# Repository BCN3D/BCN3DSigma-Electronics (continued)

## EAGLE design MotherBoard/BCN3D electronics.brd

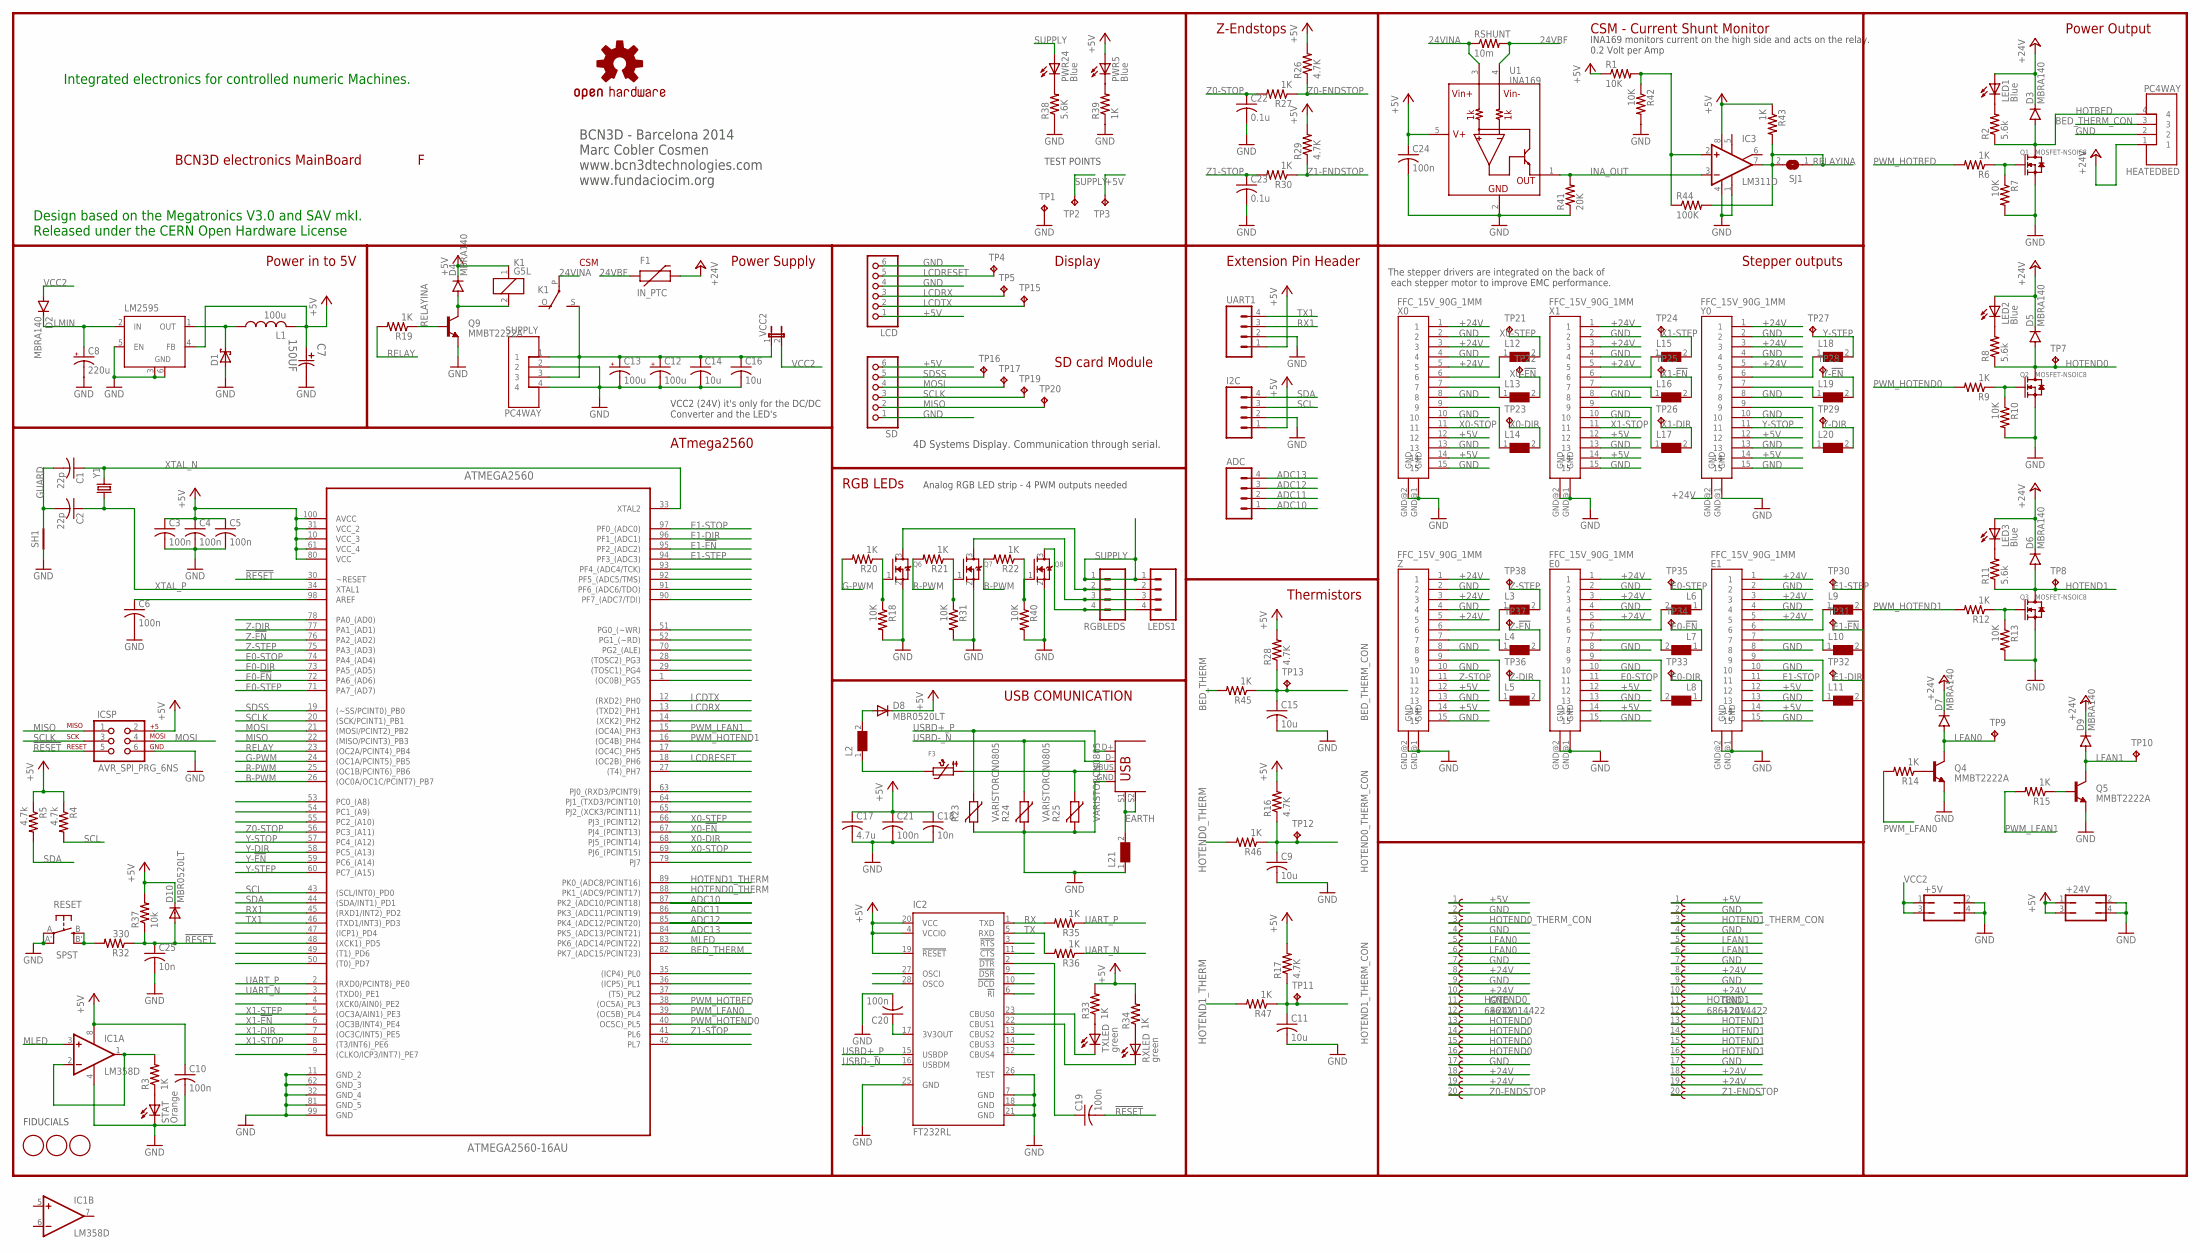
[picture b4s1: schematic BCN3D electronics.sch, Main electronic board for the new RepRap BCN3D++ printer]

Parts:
+5V, +24V: JP2Q
ADC: M04PTH; 1X04
ATMEGA2560: ATMEGA2560-16AU; QFP50P1600X1600X120-100N
C1, C2: 22p; C0805; MPN 08055A220KAT2A
C3, C4, C5, C6, C10, C19, C20, C21, C24: 100n; C0805; MPN 08055C104KAT2A
C7: 150UF; CAPAE660X610N; MPN EEEFP1A151AP
C8: 220u; UD-8X10_NICHICON; MPN EEE1VA221UAP
C9, C11, C15: 10u; C0805; MPN 08055C104KAT2A
C12, C13: 100u; UD-8X10_NICHICON; MPN EEEFC1V101AP
C14, C16: 10u; C1210K; MPN GRM32ER7YA106KA12L
C17: 4.7u; C0805; MPN 06035C103JAT2A
C18, C25: 10n; C0805; MPN 08055C103KAT2A
C22, C23: 0.1u; C0805; MPN 08055C104KAT2A
D1: SCHOTTKY-DIODESMC; SMC; MPN MBRS340T3G
D2, D3, D4, D5, D6, D7, D9: MBRA140; SMA-DIODE; MPN B140-13-F
D8, D10: MBR0520LT; SOD123; MPN DA22F2100L
E0, E1: FFC_15V_90G_1MM; TE_FFC_CON1MM
F1: IN_PTC; PTC-1206; MPN 3413.0329.22
F3: MICROBUILDER_PTC1206_L; MICROBUILDER_1206_PTC; MPN 1206L050YR
FID1, FID2, FID3: FIDUCIAL; FIDUCIAL_1MM
HEATEDBED: PC4WAY; MOLEX_MINIFIT-JR; MPN 39303045
HOTEND0, HOTEND1: 68612014422
I2C: M04PTH; 1X04
IC1: LM358D; SO08; MPN LM2904DT
IC2: FT232RL; SSOP28
IC3: LM311D; SO08
ICSP: AVR_SPI_PRG_6NS; 2X3-NS
K1: G5L; G5LE; MPN G5LA-1 5DC
L1: 100u; SSR1260; MPN SRR1260-101M
L2, L3, L4, L5, L6, L7, L8, L9, L10, L11, L12, L13, L14, L15, L16, L17, L18, L19, L20, L21: WE-CBF_0805; 0805
LCD: PINHD-1X6; 1X06
LED1, LED2, LED3: Blue; CHIPLED_0805; MPN OVS-0803
LEDS1: M04PTH; 1X04
LM2595: LM2595; TO263-5; MPN LM2595S-5.0/NOPB
LOGO1: OSHW-LOGOM; OSHW-LOGO-M
PWR5, PWR24: Blue; CHIPLED_0805; MPN OVS-0803
Q1, Q2, Q3: MOSFET-NSOIC8; SOIC8; MPN IRF8736PBF
Q4, Q5, Q9: MMBT2222A; SOT23-3; MPN BC817-40
Q6, Q7, Q8: MOSFET-NREFLOW; SOT23; MPN BSH103,215
R1, R18, R31, R40, R42: 10K; M0805; MPN CR0805-JW-102ELF
R2, R8, R11: 5.6k; M0805; MPN CR0805-JW-102ELF
R3, R39: 1K; R0805; MPN CR0805-JW-102ELF
R4, R5: 4.7k; M0805; MPN CR0805-JW-103ELF
R6, R9, R12, R14, R15, R19, R20, R21, R22, R27, R30, R33, R34, R35, R36, R43: 1K; M0805; MPN CR0805-JW-102ELF
R7, R10, R13: 10K; M0805; MPN CR0805-JW-103ELF
R16, R17, R26, R28, R29: 4.7K; M0805; MPN CR0805-FX-4701GLF
R23, R24, R25: VARISTORCN0805; CT/CN0805; MPN V5.5MLA0805LH
R32: 330; M0805; MPN CR0805-JW-103ELF
R37: 10k; M0805; MPN CR0805-JW-103ELF
R38: 5.6K; R0805; MPN CR0805-FX-4701GLF
R41: 20K; M0805; MPN CR0805-FX-4701GLF
R44: 100K; M0805; MPN CR0805-JW-102ELF
R45, R46, R47: 1K; M0805; MPN CR0805-FX-4701GLF
RESET: SPST; EVQ-Q2; MPN EVQQ2503W
RGBLEDS: M04PTH; 1X04
RSHUNT: 10m; R2512
RXLED: green; CHIPLED_0805; MPN 150080VS75000
SD: PINHD-1X6; 1X06
SH1: SHORTT5; SHORT_TOP-50
SJ1: SJ
STAT: Orange; CHIP-LED0805; MPN KP-2012SECK
SUPPLY: PC4WAY; MOLEX_MINIFIT-JR; MPN 39303045
TP1, TP2, TP3, TP4, TP5, TP7, TP8, TP9, TP10, TP11, TP12, TP13, TP15, TP16, TP17, TP19, TP20, TP21, TP22, TP23, TP24, TP25, TP26, TP27, TP28, TP29, TP30, TP31, TP32, TP33, TP34, TP35, TP36, TP37, TP38: TPB2,54; B2,54
TXLED: green; CHIPLED_0805; MPN 150080VS75000
U1: INA169; SOT23-5
U$6: USB+SHIELD; USB-B-PTH; MPN 67068-8000
UART1: M04PTH; 1X04
VCC2: JP1E; JP1
X0, X1: FFC_15V_90G_1MM; TE_FFC_CON1MM
Y0: FFC_15V_90G_1MM; TE_FFC_CON1MM
Y1: CRYSTALHC49US; HC49US; MPN 9B-16.000MAAJ-B
Z: FFC_15V_90G_1MM; TE_FFC_CON1MM

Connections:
24VBF: F1.1, RSHUNT.2, U1.4 (VIN-)
24VINA: K1.P, RSHUNT.1, U1.3 (VIN+)
!RESET: ATMEGA2560.30 (~RESET), C19.2, C25.1, D10.A, ICSP.5, R32.1, R37.1
+5V: +24V.1, +24V.3, ATMEGA2560.10 (VCC_3), ATMEGA2560.31 (VCC_2), ATMEGA2560.61 (VCC_4), ATMEGA2560.80 (VCC), ATMEGA2560.100 (AVCC), C3.1, C4.1, C5.1, C7.1, C10.1, C17.1, C18.1, C21.1, C24.1, D4.C, D8.C, D10.C, E0.12, E0.14, E1.12, E1.14, HOTEND0.1, HOTEND1.1, I2C.1, IC1.8 (V+), IC2.4 (VCCIO), IC2.19 (!RESET), IC2.20 (VCC), IC3.8 (V+), ICSP.2, K1.1, L1.B (2), LCD.1, LM2595.4 (FB), PWR5.A, R1.1, R4.1, R5.1, R16.2, R17.2, R26.2, R28.2, R29.2, R33.2, R34.2, R37.2, R43.1, SD.6, TP3.TP, U1.5 (V+), UART1.1, X0.12, X0.14, X1.12, X1.14, Y0.12, Y0.14, Z.12, Z.14
+24V: D3.C, D5.C, D6.C, D7.C, D9.C, E0.1, E0.3, E0.5, E1.1, E1.3, E1.5, F1.2, HEATEDBED.1, HOTEND0.8, HOTEND0.10, HOTEND0.12, HOTEND0.18, HOTEND0.19, HOTEND1.8, HOTEND1.10, HOTEND1.12, HOTEND1.18, HOTEND1.19, LED1.A, LED2.A, LED3.A, X0.1, X0.3, X0.5, X1.1, X1.3, X1.5, Y0.1, Y0.3, Y0.5, Y0.GND@2 (GND), Z.1, Z.3, Z.5
ADC10: ADC.1, ATMEGA2560.87 (PK2_(ADC10/PCINT18))
ADC11: ADC.2, ATMEGA2560.86 (PK3_(ADC11/PCINT19))
ADC12: ADC.3, ATMEGA2560.85 (PK4_(ADC12/PCINT20))
ADC13: ADC.4, ATMEGA2560.84 (PK5_(ADC13/PCINT21))
B-PWM: ATMEGA2560.26 ((OC0A/OC1C/PCINT7)_PB7), R22.2
BED_THERM: ATMEGA2560.82 (PK7_(ADC15/PCINT23)), R45.2
BED_THERM_CON: C15.1, HEATEDBED.3, R28.1, R45.1, TP13.TP
E0-!EN: ATMEGA2560.72 (PA6_(AD6)), L7.1, TP34.TP
E0-DIR: ATMEGA2560.73 (PA5_(AD5)), L8.1, TP33.TP
E0-STEP: ATMEGA2560.71 (PA7_(AD7)), L6.1, TP35.TP
E0-STOP: ATMEGA2560.74 (PA4_(AD4)), E0.11
E1-!EN: ATMEGA2560.95 (PF2_(ADC2)), L10.2, TP31.TP
E1-DIR: ATMEGA2560.96 (PF1_(ADC1)), L11.2, TP32.TP
E1-STEP: ATMEGA2560.94 (PF3_(ADC3)), L9.2, TP30.TP
E1-STOP: ATMEGA2560.97 (PF0_(ADC0)), E1.11
EARTH: L21.2, U$6.S1, U$6.S2
G-PWM: ATMEGA2560.24 ((OC1A/PCINT5)_PB5), R20.2
GND: +5V.2, +5V.4, +24V.2, +24V.4, ATMEGA2560.11 (GND_2), ATMEGA2560.32 (GND_4), ATMEGA2560.62 (GND_3), ATMEGA2560.81 (GND_5), ATMEGA2560.99 (GND), C3.2, C4.2, C5.2, C6.2, C7.2, C8.-, C9.2, C10.2, C11.2, C12.-, C13.-, C14.2, C15.2, C16.2, C17.2, C18.2, C20.2, C21.2, C22.2, C23.2, C24.2, C25.2, D1.A, E0.2, E0.4, E0.8, E0.10, E0.13, E0.15, E0.GND@1 (GND), E0.GND@2 (GND), E1.2, E1.4, E1.8, E1.10, E1.13, E1.15, E1.GND@1 (GND), E1.GND@2 (GND), HEATEDBED.2, HOTEND0.2, HOTEND0.4, HOTEND0.7, HOTEND0.9, HOTEND0.11, HOTEND0.17, HOTEND1.2, HOTEND1.4, HOTEND1.7, HOTEND1.9, HOTEND1.11, HOTEND1.17, I2C.2, IC1.4 (V-), IC2.7 (GND), IC2.18 (GND), IC2.21 (GND), IC2.25 (GND), IC2.26 (TEST), IC3.1 (GND), IC3.4 (V-), ICSP.6, L21.1, LCD.4, LCD.6, LM2595.3 (GND), LM2595.5 (EN), LM2595.6 (GND), Q1.1 (S), Q1.2 (S), Q1.3 (S), Q2.1 (S), Q2.2 (S), Q2.3 (S), Q3.1 (S), Q3.2 (S), Q3.3 (S), Q4.2 (E), Q5.2 (E), Q6.2 (S), Q7.2 (S), Q8.2 (S), Q9.2 (E), R7.2, R10.2, R13.2, R18.2, R23.2, R24.2, R25.2, R31.2, R38.1, R39.1, R40.2, R41.1, R42.2, RESET.A, RESET.A' (P1), SD.1, SH1.1, STAT.C, SUPPLY.2, SUPPLY.4, TP1.TP, U1.2 (GND), U$6.GND, UART1.2, X0.2, X0.4, X0.8, X0.10, X0.13, X0.15, X0.GND@1 (GND), X0.GND@2 (GND), X1.2, X1.4, X1.8, X1.10, X1.13, X1.15, X1.GND@1 (GND), X1.GND@2 (GND), Y0.2, Y0.4, Y0.8, Y0.10, Y0.13, Y0.15, Y0.GND@1 (GND), Z.2, Z.4, Z.8, Z.10, Z.13, Z.15, Z.GND@1 (GND), Z.GND@2 (GND)
GUARD: C1.2, C2.2, SH1.2
HOTBED: D3.A, HEATEDBED.4, Q1.5 (D), Q1.6 (D), Q1.7 (D), Q1.8 (D), R2.1
HOTEND0: D5.A, HOTEND0.13, HOTEND0.14, HOTEND0.15, HOTEND0.16, Q2.5 (D), Q2.6 (D), Q2.7 (D), Q2.8 (D), R8.1, TP7.TP
HOTEND0_THERM: ATMEGA2560.88 (PK1_(ADC9/PCINT17)), R46.2
HOTEND0_THERM_CON: C9.1, HOTEND0.3, R16.1, R46.1, TP12.TP
HOTEND1: D6.A, HOTEND1.13, HOTEND1.14, HOTEND1.15, HOTEND1.16, Q3.5 (D), Q3.6 (D), Q3.7 (D), Q3.8 (D), R11.1, TP8.TP
HOTEND1_THERM: ATMEGA2560.89 (PK0_(ADC8/PCINT16)), R47.2
HOTEND1_THERM_CON: C11.1, HOTEND1.3, R17.1, R47.1, TP11.TP
INA_OUT: IC3.3 (-IN), R41.2, U1.1 (OUT)
LCDRESET: ATMEGA2560.18 ((OC2B)_PH6), LCD.5, TP4.TP
LCDRX: ATMEGA2560.13 ((TXD2)_PH1), LCD.3, TP5.TP
LCDTX: ATMEGA2560.12 ((RXD2)_PH0), LCD.2, TP15.TP
LFAN0: D7.A, HOTEND0.5, HOTEND0.6, Q4.3 (C), TP9.TP
LFAN1: D9.A, HOTEND1.5, HOTEND1.6, Q5.3 (C), TP10.TP
LMIN: C8.+, D2.C, LM2595.2 (IN)
MISO: ATMEGA2560.22 ((MISO/PCINT3)_PB3), ICSP.1, SD.2, TP20.TP
MLED: ATMEGA2560.83 (PK6_(ADC14/PCINT22)), IC1.3 (+IN)
MOSI: ATMEGA2560.21 ((MOSI/PCINT2)_PB2), ICSP.4, SD.4, TP17.TP
unnamed: C19.1, IC2.2 (!DTR)
unnamed: ATMEGA2560.98 (AREF), C6.1
unnamed: L12.1, X0.6
unnamed: IC2.23 (CBUS0), TXLED.C
unnamed: IC2.22 (CBUS1), RXLED.C
unnamed: LEDS1.2, Q6.3 (D), RGBLEDS.2
unnamed: LEDS1.3, Q7.3 (D), RGBLEDS.3
unnamed: LEDS1.4, Q8.3 (D), RGBLEDS.4
unnamed: R32.2, RESET.B (S), RESET.B' (S1)
unnamed: D8.A, L2.2
unnamed: IC1.1 (OUT), IC1.2 (-IN), R3.2
unnamed: Q6.1 (G), R18.1, R20.1
unnamed: R3.1, STAT.A
unnamed: Q7.1 (G), R21.1, R31.1
unnamed: Q8.1 (G), R22.1, R40.1
unnamed: L13.1, X0.7
unnamed: L14.1, X0.9
unnamed: L18.1, Y0.6
unnamed: L19.1, Y0.7
unnamed: L20.1, Y0.9
unnamed: L15.1, X1.6
unnamed: L16.1, X1.7
unnamed: L17.1, X1.9
unnamed: E0.6, L6.2
unnamed: E0.7, L7.2
unnamed: E0.9, L8.2
unnamed: F3.2, L2.1
unnamed: IC3.2 (+IN), R1.2, R42.1, R44.1
unnamed: L3.1, Z.6
unnamed: L4.1, Z.7
unnamed: L5.1, Z.9
unnamed: E1.9, L11.1
unnamed: E1.7, L10.1
unnamed: E1.6, L9.1
unnamed: LED1.C, R2.2
unnamed: Q1.4 (G), R6.1, R7.1
unnamed: C20.1, IC2.17 (3V3OUT)
unnamed: R33.1, TXLED.A
unnamed: R34.1, RXLED.A
unnamed: Q4.1 (B), R14.1
unnamed: LED2.C, R8.2
unnamed: Q2.4 (G), R9.1, R10.1
unnamed: D4.A, K1.2, Q9.3 (C)
unnamed: LED3.C, R11.2
unnamed: Q3.4 (G), R12.1, R13.1
unnamed: Q5.1 (B), R15.1
unnamed: PWR24.C, R38.2
unnamed: PWR5.C, R39.2
OUT: D1.C, L1.A (1), LM2595.1 (OUT)
PWM_HOTBED: ATMEGA2560.38 ((OC5A)_PL3), R6.2
PWM_HOTEND0: ATMEGA2560.40 (OC5C)_PL5), R9.2
PWM_HOTEND1: ATMEGA2560.16 ((OC4B)_PH4), R12.2
PWM_LFAN0: ATMEGA2560.39 ((OC5B)_PL4), R14.2
PWM_LFAN1: ATMEGA2560.15 ((OC4A)_PH3), R15.2
R-PWM: ATMEGA2560.25 ((OC1B/PCINT6)_PB6), R21.2
RELAY: ATMEGA2560.23 ((OC2A/PCINT4)_PB4), R19.2
RELAYINA: IC3.7 (OUT), Q9.1 (B), R19.1, R43.2, R44.2, SJ1.1, SJ1.2
RX: IC2.1 (TXD), R35.2
RX1: ATMEGA2560.45 ((RXD1/INT2)_PD2), UART1.3
SCL: ATMEGA2560.43 ((SCL/INT0)_PD0), I2C.3, R4.2
SCLK: ATMEGA2560.20 ((SCK/PCINT1)_PB1), ICSP.3, SD.3, TP19.TP
SDA: ATMEGA2560.44 ((SDA/INT1)_PD1), I2C.4, R5.2
SDSS: ATMEGA2560.19 ((~SS/PCINT0)_PB0), SD.5, TP16.TP
SUPPLY: C12.+, C13.+, C14.1, C16.1, K1.S, LEDS1.1, PWR24.A, RGBLEDS.1, SUPPLY.1, SUPPLY.3, TP2.TP, VCC2.1
TX: IC2.5 (RXD), R36.2
TX1: ATMEGA2560.46 ((TXD1/INT3)_PD3), UART1.4
UART_N: ATMEGA2560.3 ((TXD0)_PE1), R36.1
UART_P: ATMEGA2560.2 ((RXD0/PCINT8)_PE0), R35.1
USBD+_P: IC2.15 (USBDP), R23.1, U$6.D+
USBD-_N: IC2.16 (USBDM), R24.1, U$6.D-
VBUS: F3.1, R25.1, U$6.VBUS
VCC2: +5V.1, +5V.3, D2.A, VCC2.2
X0-!EN: ATMEGA2560.67 (PJ4_(PCINT13)), L13.2, TP22.TP
X0-DIR: ATMEGA2560.68 (PJ5_(PCINT14)), L14.2, TP23.TP
X0-STEP: ATMEGA2560.66 (PJ3_(PCINT12)), L12.2, TP21.TP
X0-STOP: ATMEGA2560.69 (PJ6_(PCINT15)), X0.11
X1-!EN: ATMEGA2560.6 ((OC3B/INT4)_PE4), L16.2, TP25.TP
X1-DIR: ATMEGA2560.7 ((OC3C/INT5)_PE5), L17.2, TP26.TP
X1-STEP: ATMEGA2560.5 ((OC3A/AIN1)_PE3), L15.2, TP24.TP
X1-STOP: ATMEGA2560.8 ((T3/INT6)_PE6), X1.11
XTAL_N: ATMEGA2560.33 (XTAL2), C1.1, Y1.2
XTAL_P: ATMEGA2560.34 (XTAL1), C2.1, Y1.1
Y-!EN: ATMEGA2560.59 (PC6_(A14)), L19.2, TP28.TP
Y-DIR: ATMEGA2560.58 (PC5_(A13)), L20.2, TP29.TP
Y-STEP: ATMEGA2560.60 (PC7_(A15)), L18.2, TP27.TP
Y-STOP: ATMEGA2560.57 (PC4_(A12)), Y0.11
Z0-ENDSTOP: HOTEND0.20, R26.1, R27.1
Z0-STOP: ATMEGA2560.56 (PC3_(A11)), C22.1, R27.2
Z1-ENDSTOP: HOTEND1.20, R29.1, R30.1
Z1-STOP: ATMEGA2560.41 (PL6), C23.1, R30.2
Z-!EN: ATMEGA2560.76 (PA2_(AD2)), L4.2, TP37.TP
Z-DIR: ATMEGA2560.77 (PA1_(AD1)), L5.2, TP36.TP
Z-STEP: ATMEGA2560.75 (PA3_(AD3)), L3.2, TP38.TP
Z-STOP: Z.11

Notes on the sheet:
Power Output
Thermistors
USB COMUNICATION
ATmega2560
Power in to 5V
Power Supply
Display
TEST POINTS
FIDUCIALS
SD card Module
Extension Pin Header
4D Systems Display. Communication through serial.
BCN3D - Barcelona 2014 Marc Cobler Cosmen www.bcn3dtechnologies.com www.fundaciocim.org
Design based on the Megatronics V3.0 and SAV mkI. Released under the CERN Open Hardware License
Integrated electronics for controlled numeric Machines.
Stepper outputs
The stepper drivers are integrated on the back of each stepper motor to improve EMC performance.
BCN3D electronics MainBoard
RGB LEDs
Analog RGB LED strip - 4 PWM outputs needed
VCC2 (24V) it's only for the DC/DC Converter and the LED's
Z-Endstops
CSM - Current Shunt Monitor
INA169 monitors current on the high side and acts on the relay. 0.2 Volt per Amp
CSM

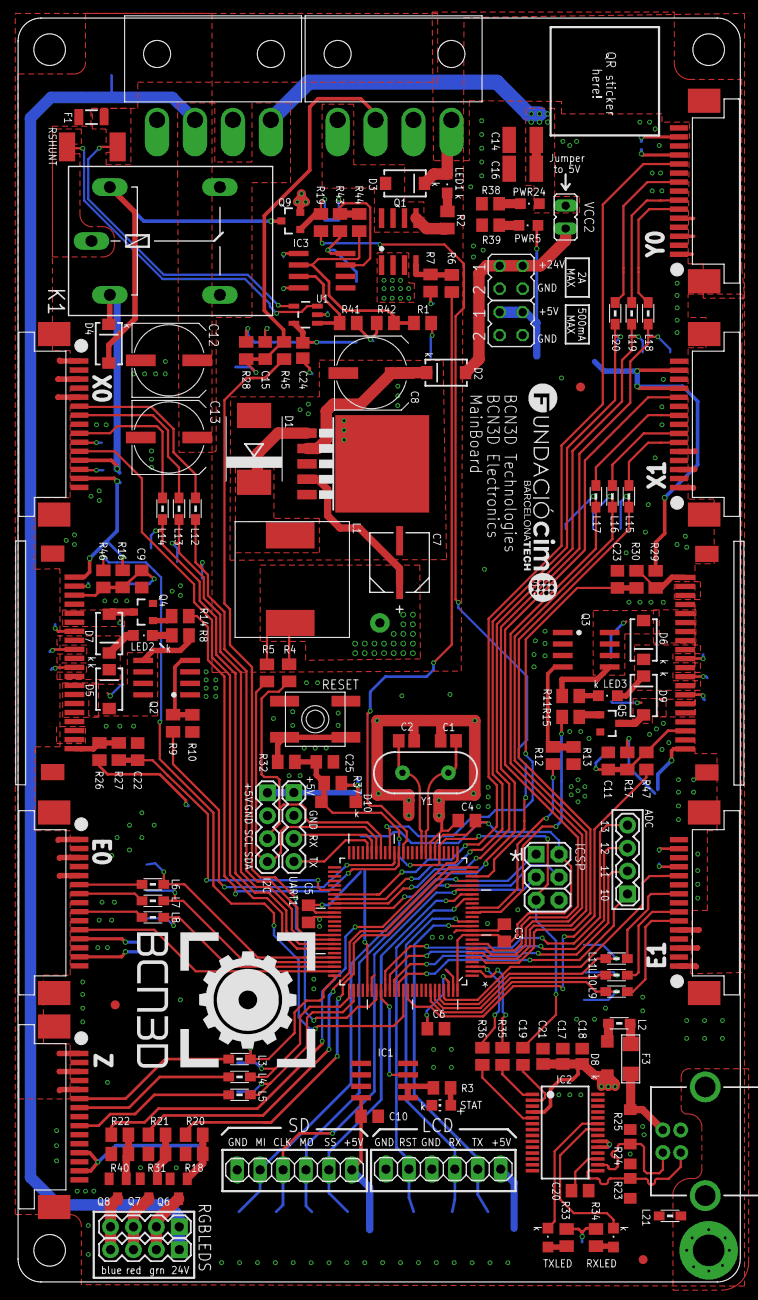
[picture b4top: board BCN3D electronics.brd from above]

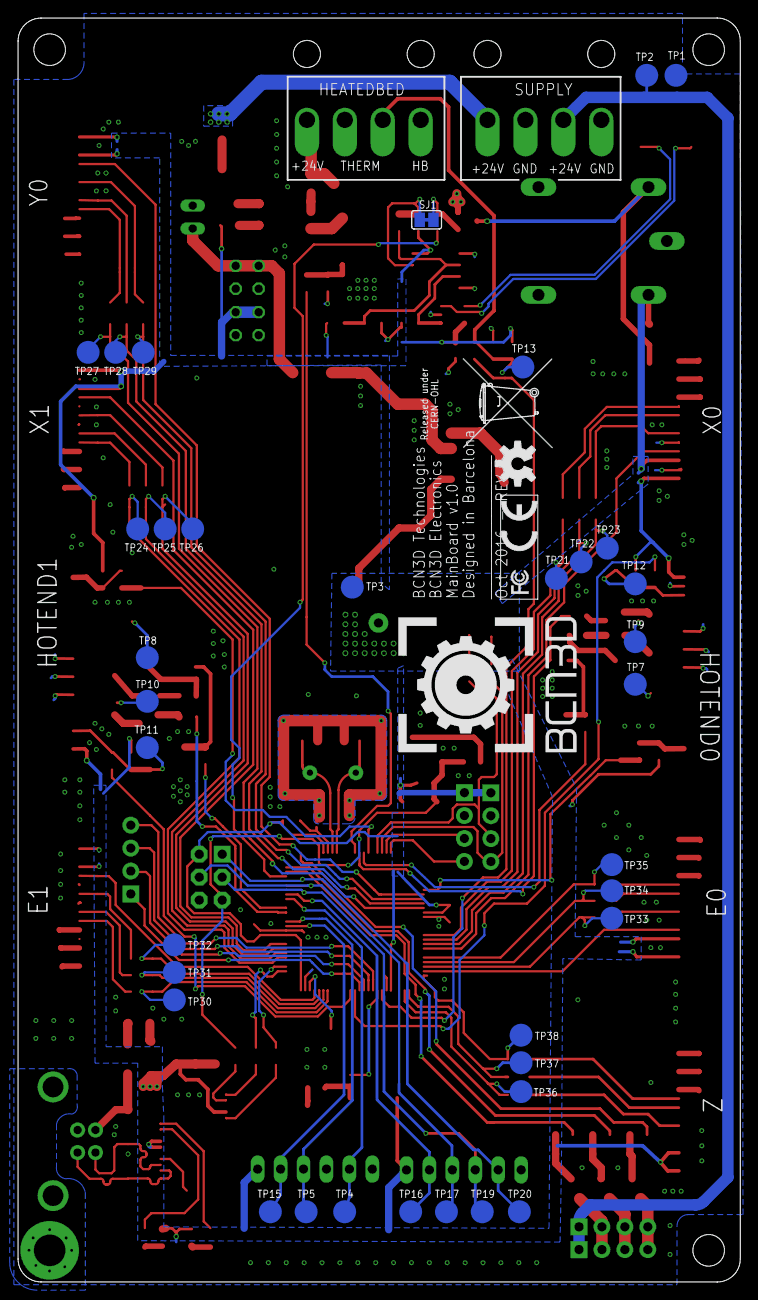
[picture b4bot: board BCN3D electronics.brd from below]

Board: 2 copper layers, 80.0 x 140.0 mm, 201 parts (41 on the bottom side), 134 nets.

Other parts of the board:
U$2: TONNE_10.00
U$3: FCC_10X4.175MM
U$4: CE-4MM
U$5, U$8: BCN3D_LOGO
U$9: FCIM_LOGO

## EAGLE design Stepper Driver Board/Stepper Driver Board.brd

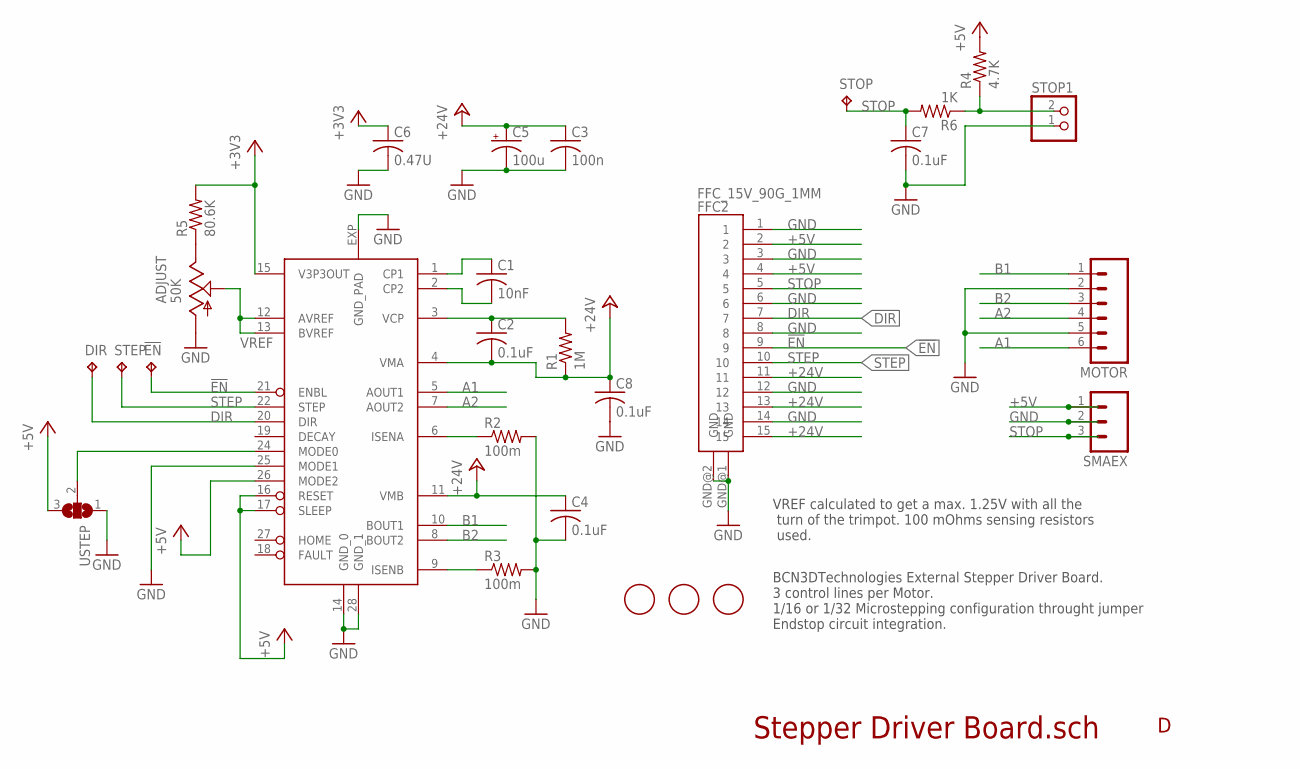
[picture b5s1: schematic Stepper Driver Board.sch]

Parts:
!EN: TPB1,27; B1,27
ADJUST: 50K; 3223G; MPN TC33X-2-503E
C1: 10nF; C0805; MPN 06035C103JAT2A
C2, C4, C7, C8: 0.1uF; C0805; MPN 08055C104K4Z2A
C3: 100n; C0805; MPN 08055C104K4Z2A
C5: 100u; UD-6,3X7,7_NICHICON; MPN EEE1HA101UAP
C6: 0.47U; C0805; MPN C0805C474K5RACTU
DIR: TPB1,27; B1,27
FFC2: FFC_15V_90G_1MM; TE_FFC_CON1MM
IC1: DRV8825PWP; TSSOP-28; MPN DRV8825PWP
MOTOR: M06; JST-6-PTH
R1: 1M; R0805; MPN MC0805S8F1004T5E
R2, R3: 100m; R1210; MPN ERJ14BSFR10U
R4: 4.7K; R0805; MPN ERJP06F4701V
R5: 80.6K; R0805; MPN CRCW080580K6FKEA
R6: 1K; R0805; MPN CR0805-JW-102ELF
SMAEX: M03PTH; 1X03
STEP: TPB1,27; B1,27
STOP: TPB1,27; B1,27
STOP1: JST_2PIN-THM-RA; JST-PH-2-THM-RA
U$2, U$3, U$4: FIDUCIAL; FIDUCIAL_1MM
USTEP: SJ2W; SJ_2

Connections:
!EN: !EN.TP, FFC2.9, IC1.21 (ENBL)
+3V3: C6.1, IC1.15 (V3P3OUT), R5.2
+5V: FFC2.2, FFC2.4, IC1.16 (RESET), IC1.17 (SLEEP), IC1.26 (MODE2), R4.2, SMAEX.1, USTEP.3
+24V: C2.2, C3.1, C4.1, C5.+, C8.1, FFC2.11, FFC2.13, FFC2.15, IC1.4 (VMA), IC1.11 (VMB), R1.1
A1: IC1.5 (AOUT1), MOTOR.6
A2: IC1.7 (AOUT2), MOTOR.4
B1: IC1.10 (BOUT1), MOTOR.1
B2: IC1.8 (BOUT2), MOTOR.3
DIR: DIR.TP, FFC2.7, IC1.20 (DIR)
GND: ADJUST.1 (A), C3.2, C4.2, C5.-, C6.2, C7.2, C8.2, FFC2.1, FFC2.3, FFC2.6, FFC2.8, FFC2.12, FFC2.14, FFC2.GND@1 (GND), FFC2.GND@2 (GND), IC1.14 (GND_0), IC1.25 (MODE1), IC1.28 (GND_1), IC1.EXP (GND_PAD), MOTOR.2, MOTOR.5, R2.2, R3.2, SMAEX.2, STOP1.1 (2), USTEP.1
unnamed: ADJUST.3 (E), R5.1
unnamed: IC1.24 (MODE0), USTEP.2
unnamed: IC1.6 (ISENA), R2.1
unnamed: IC1.9 (ISENB), R3.1
unnamed: C1.1, IC1.1 (CP1)
unnamed: C1.2, IC1.2 (CP2)
unnamed: C2.1, IC1.3 (VCP), R1.2
unnamed: R4.1, R6.1, STOP1.2 (1)
STEP: FFC2.10, IC1.22 (STEP), STEP.TP
STOP: C7.1, FFC2.5, R6.2, SMAEX.3, STOP.TP
VREF: ADJUST.2 (S), IC1.12 (AVREF), IC1.13 (BVREF)

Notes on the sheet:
Stepper Driver Board.sch
BCN3DTechnologies External Stepper Driver Board. 3 control lines per Motor. 1/16 or 1/32 Microstepping configuration throught jumper Endstop circuit integration.
VREF calculated to get a max. 1.25V with all the turn of the trimpot. 100 mOhms sensing resistors used.

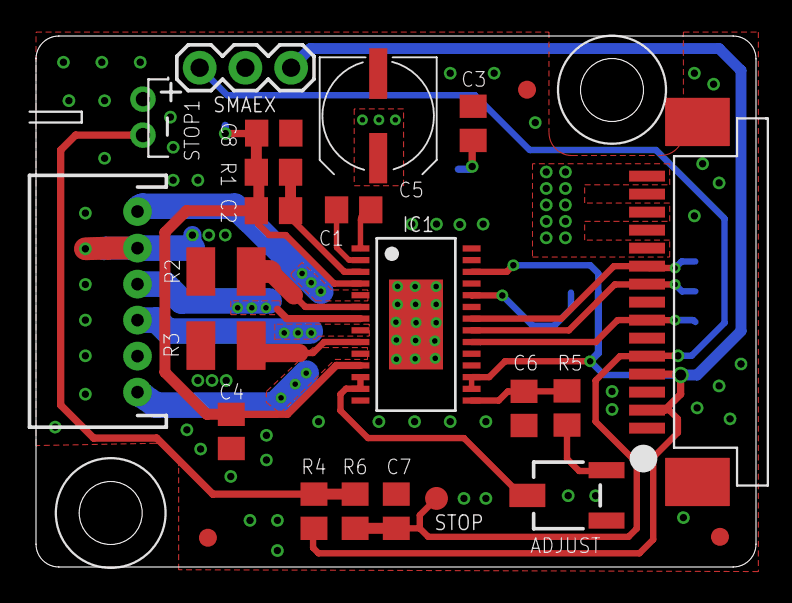
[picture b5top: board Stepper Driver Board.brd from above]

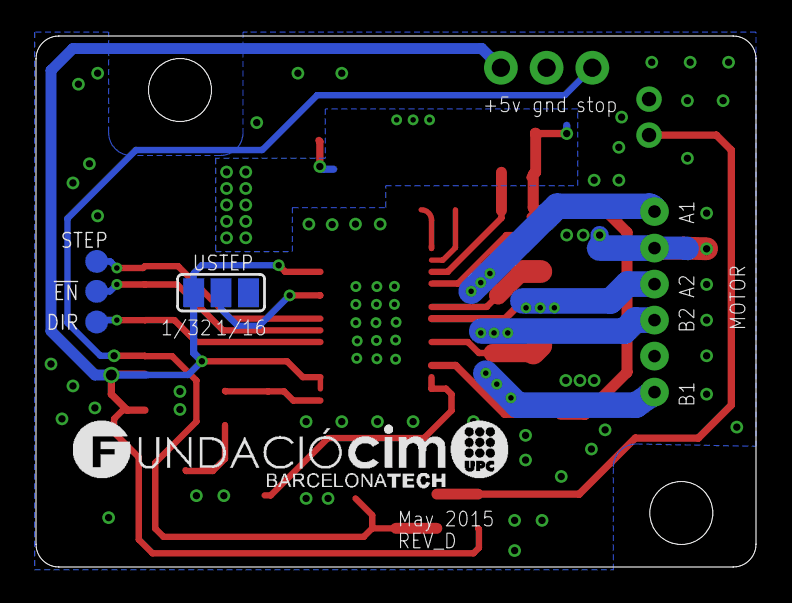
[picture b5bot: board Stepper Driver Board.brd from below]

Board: 2 copper layers, 40.0 x 29.5 mm, 29 parts (5 on the bottom side), 21 nets.

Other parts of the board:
U$5: FCIM_LOGO

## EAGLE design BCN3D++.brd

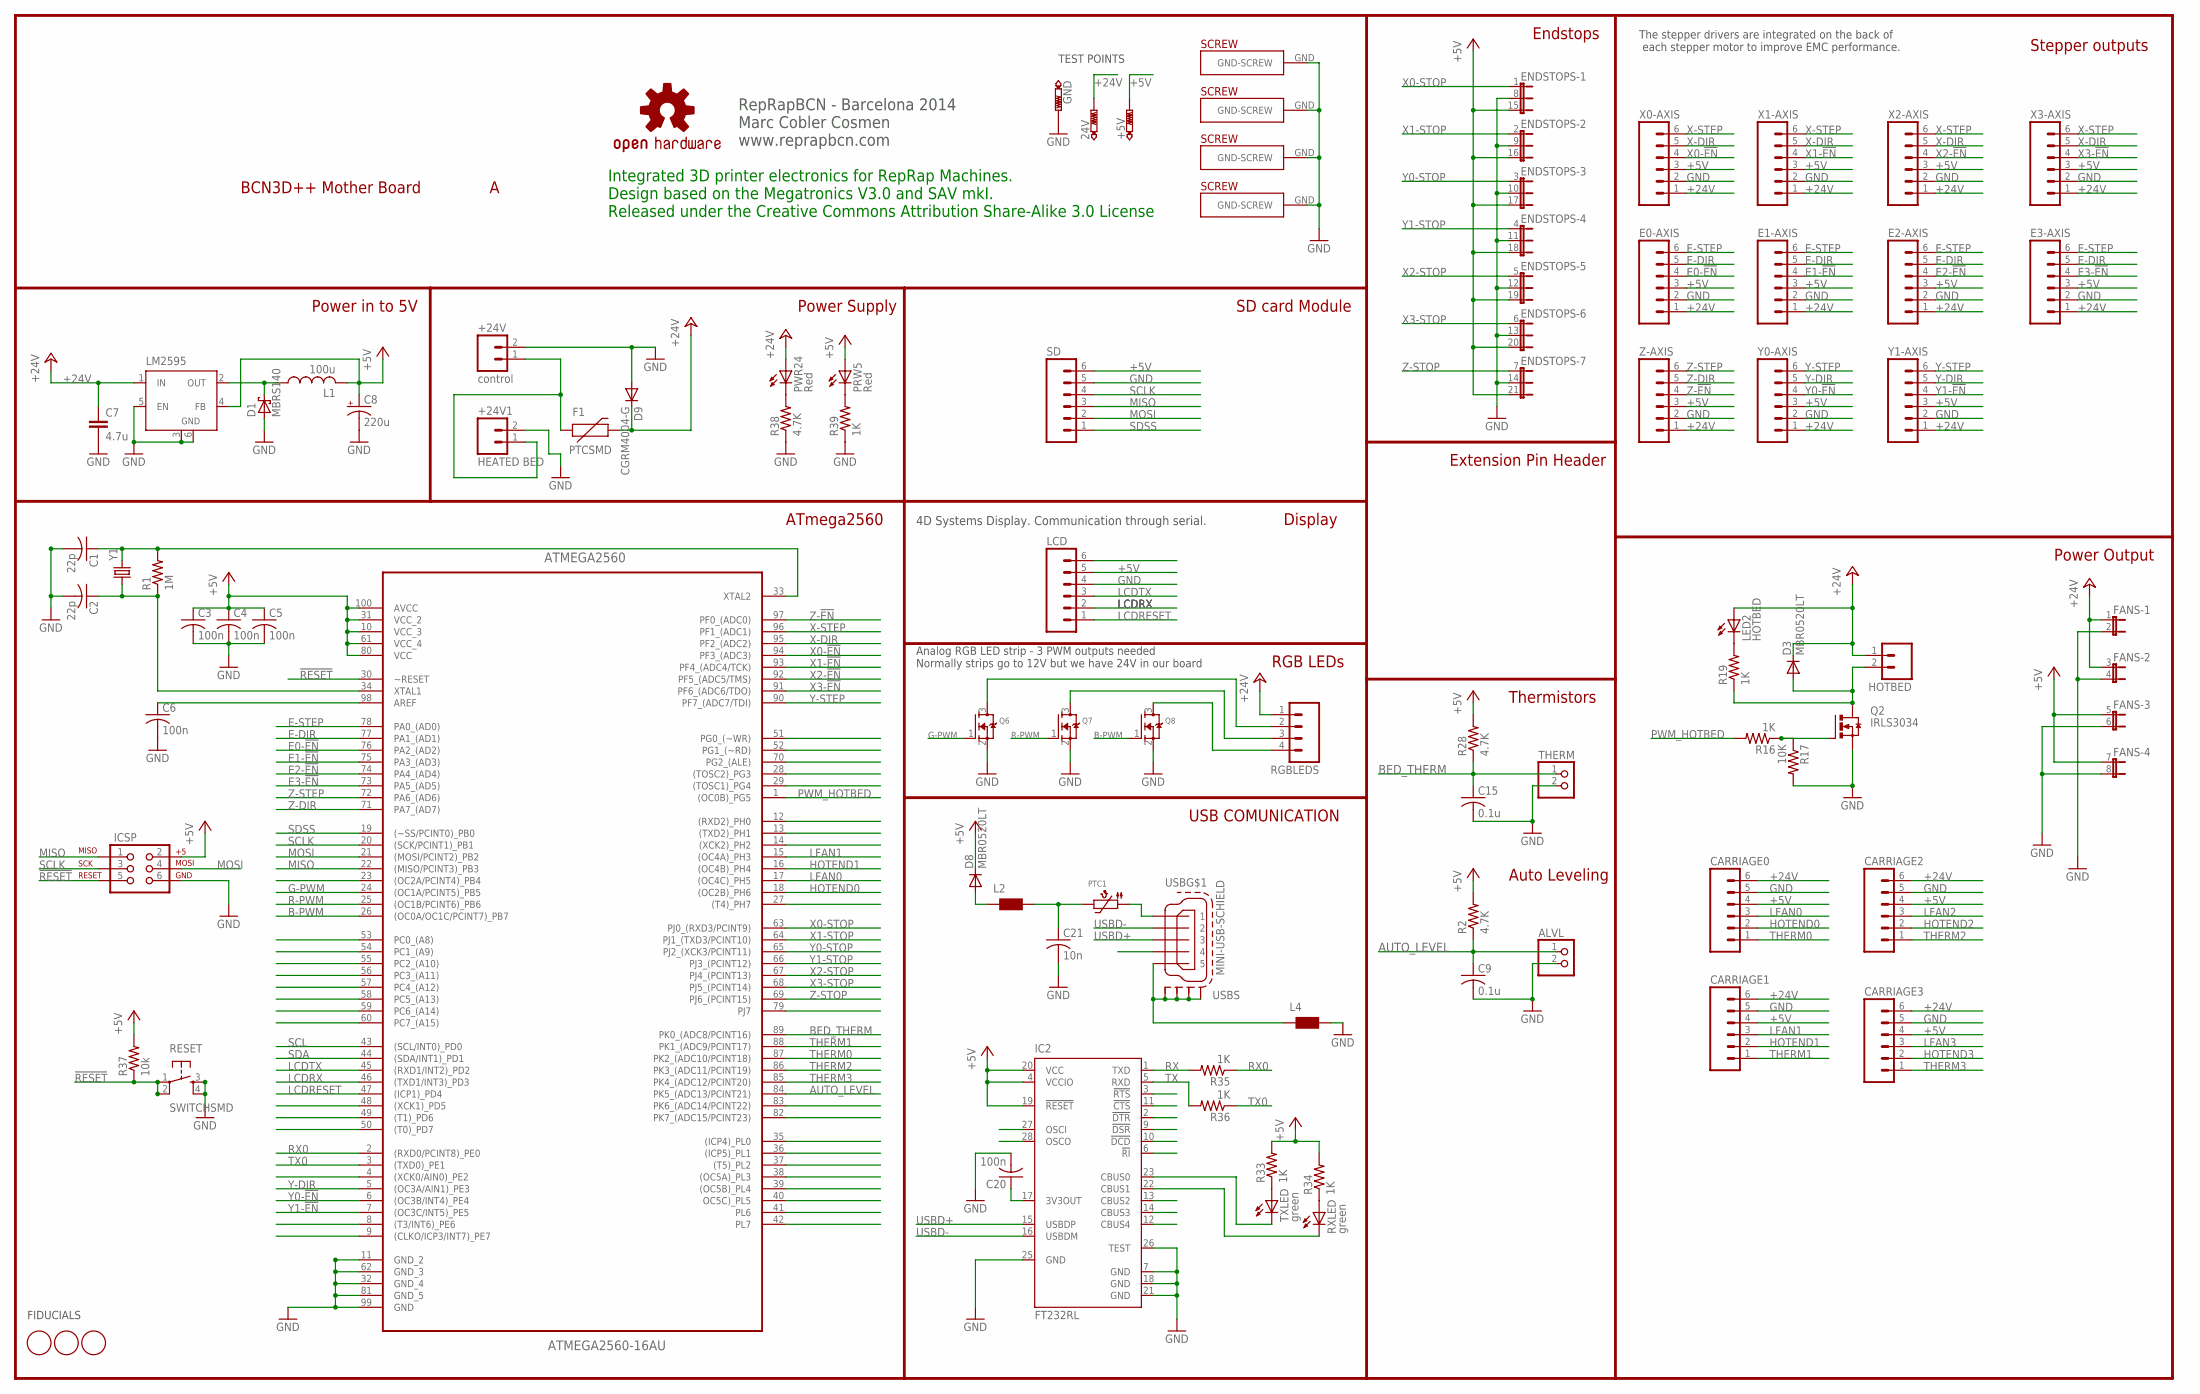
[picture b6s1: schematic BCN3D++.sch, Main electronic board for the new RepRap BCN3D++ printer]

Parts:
24V: PTR1TP12SQ; TP12SQ
+5V: PTR1TP12SQ; TP12SQ
+24V: control; SCREWTERMINAL-5MM-2
+24V1: HEATED BED; SCREWTERMINAL-5MM-2
ALVL: PINHD-1X2; 1X02
ATMEGA2560: ATMEGA2560-16AU; QFP50P1600X1600X120-100N
C1, C2: 22p; C0805
C3, C4, C5, C6, C20: 100n; C0805
C7: 4.7u; C1206K
C8: 220u; UD-8X10_NICHICON
C9, C15: 0.1u; C0805
C21: 10n; C0805K
CARRIAGE0, CARRIAGE1, CARRIAGE2, CARRIAGE3: M06SIP; 1X06
D1: MBRS140; DO-214AA
D3, D8: MBR0520LT; SOD123
D9: CGRM4004-G; SOD-123_MINI-SMA
E0-AXIS, E1-AXIS, E2-AXIS, E3-AXIS: M06SIP; 1X06
ENDSTOPS: PINCONNECTOR-7X3; MALE-PIN-3X7
F1: PTCSMD; PTC-1206
FANS: JP4QE; JP4Q
FID1, FID2, FID3: FIDUCIAL; FIDUCIAL_1MM
GND: PTR1TP12SQ; TP12SQ
HOTBED: M025MM; SCREWTERMINAL-5MM-2
IC2: FT232RL; SSOP28
ICSP: AVR_SPI_PRG_6NS; 2X3-NS
L1: 100u; SSR1260
L2, L4: WUERTH-ELEKTRONIK_WE-CBF_1206W; WUERTH-ELEKTRONIK_1206W
LCD: M06SIP; 1X06
LED2: HOTBED; CHIP-LED0603
LM2595: LM2596S; TO263-5
LOGO1: OSHW-LOGOM; OSHW-LOGO-M
PRW5: Red; CHIP-LED0805
PTC1: MICROBUILDER_PTC1206_L; MICROBUILDER_1206_PTC
PWR24: Red; CHIP-LED0805
Q2: IRLS3034; D2PACK
Q6, Q7, Q8: MOSFET-NREFLOW; SOT23
R1: 1M; R0805
R2, R28: 4.7K; M0805
R16, R19, R33, R34, R35, R36: 1K; M0805
R17: 10K; M0805
R37: 10k; M0805
R38: 4.7K; R0805
R39: 1K; R0805
RESET: SWITCHSMD; TACTILE-SWITCH-SMD
RGBLEDS: M04PTH; 1X04
RXLED: green; CHIP-LED0603
SD: M06SIP; 1X06
THERM: PINHD-1X2; 1X02
TXLED: green; CHIP-LED0603
U$1, U$2, U$3, U$4: SANGUINOLOLU_PLATED-SCREW; SANGUINOLOLU_PLATEDSCREW
USB: MINI-USB-SCHIELD; 32005-201
X0-AXIS, X1-AXIS, X2-AXIS, X3-AXIS: M06SIP; 1X06
Y0-AXIS, Y1-AXIS: M06SIP; 1X06
Y1: CRYSTALHC49US; HC49US
Z-AXIS: M06SIP; 1X06

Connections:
11111: ATMEGA2560.23 ((OC2A/PCINT4)_PB4)
!RESET: ATMEGA2560.30 (~RESET), ICSP.5, R37.1, RESET.1, RESET.2
+5V: +5V.TP, ATMEGA2560.10 (VCC_3), ATMEGA2560.31 (VCC_2), ATMEGA2560.61 (VCC_4), ATMEGA2560.80 (VCC), ATMEGA2560.100 (AVCC), C3.1, C4.1, C5.1, C8.+, CARRIAGE0.4, CARRIAGE1.4, CARRIAGE2.4, CARRIAGE3.4, D8.C, E0-AXIS.3, E1-AXIS.3, E2-AXIS.3, E3-AXIS.3, ENDSTOPS.15 (3), ENDSTOPS.16 (3), ENDSTOPS.17 (3), ENDSTOPS.18 (3), ENDSTOPS.19 (3), ENDSTOPS.20 (3), ENDSTOPS.21 (3), FANS.5 (1), FANS.7 (1), IC2.4 (VCCIO), IC2.19 (!RESET), IC2.20 (VCC), ICSP.2, L1.B (2), LCD.5, LM2595.4 (FB), PRW5.A, R2.2, R28.2, R33.2, R34.2, R37.2, SD.6, X0-AXIS.3, X1-AXIS.3, X2-AXIS.3, X3-AXIS.3, Y0-AXIS.3, Y1-AXIS.3, Z-AXIS.3
+24V: 24V.TP, C7.1, CARRIAGE0.6, CARRIAGE1.6, CARRIAGE2.6, CARRIAGE3.6, D3.C, D9.C, E0-AXIS.1, E1-AXIS.1, E2-AXIS.1, E3-AXIS.1, F1.2, FANS.1, FANS.3 (1), HOTBED.1, LED2.A, LM2595.1 (IN), PWR24.A, RGBLEDS.1, X0-AXIS.1, X1-AXIS.1, X2-AXIS.1, X3-AXIS.1, Y0-AXIS.1, Y1-AXIS.1, Z-AXIS.1
AUTO_LEVEL: ALVL.1, ATMEGA2560.84 (PK5_(ADC13/PCINT21)), C9.1, R2.1
B-PWM: ATMEGA2560.26 ((OC0A/OC1C/PCINT7)_PB7), Q8.1 (G)
BED_THERM: ATMEGA2560.89 (PK0_(ADC8/PCINT16)), C15.1, R28.1, THERM.1
E0-!EN: ATMEGA2560.76 (PA2_(AD2)), E0-AXIS.4
E1-!EN: ATMEGA2560.75 (PA3_(AD3)), E1-AXIS.4
E2-!EN: ATMEGA2560.74 (PA4_(AD4)), E2-AXIS.4
E3-!EN: ATMEGA2560.73 (PA5_(AD5)), E3-AXIS.4
E-DIR: ATMEGA2560.77 (PA1_(AD1)), E0-AXIS.5, E1-AXIS.5, E2-AXIS.5, E3-AXIS.5
E-STEP: ATMEGA2560.78 (PA0_(AD0)), E0-AXIS.6, E1-AXIS.6, E2-AXIS.6, E3-AXIS.6
G-PWM: ATMEGA2560.24 ((OC1A/PCINT5)_PB5), Q6.1 (G)
GND: +24V.2, +24V1.2, ALVL.2, ATMEGA2560.11 (GND_2), ATMEGA2560.32 (GND_4), ATMEGA2560.62 (GND_3), ATMEGA2560.81 (GND_5), ATMEGA2560.99 (GND), C1.2, C2.2, C3.2, C4.2, C5.2, C6.2, C7.2, C8.-, C9.2, C15.2, C20.2, C21.2, CARRIAGE0.5, CARRIAGE1.5, CARRIAGE2.5, CARRIAGE3.5, D1.A, D9.A, E0-AXIS.2, E1-AXIS.2, E2-AXIS.2, E3-AXIS.2, ENDSTOPS.8 (2), ENDSTOPS.9 (2), ENDSTOPS.10 (2), ENDSTOPS.11 (2), ENDSTOPS.12 (2), ENDSTOPS.13 (2), ENDSTOPS.14 (2), FANS.2, FANS.4 (2), FANS.6 (2), FANS.8 (2), GND.TP, IC2.7 (GND), IC2.18 (GND), IC2.21 (GND), IC2.25 (GND), IC2.26 (TEST), ICSP.6, L4.2, LCD.4, LM2595.3 (GND), LM2595.5 (EN), LM2595.6 (GND), Q2.3 (S), Q6.2 (S), Q7.2 (S), Q8.2 (S), R17.2, R38.1, R39.1, RESET.3, RESET.4, SD.5, THERM.2, U$1.GND, U$2.GND, U$3.GND, U$4.GND, X0-AXIS.2, X1-AXIS.2, X2-AXIS.2, X3-AXIS.2, Y0-AXIS.2, Y1-AXIS.2, Z-AXIS.2
HOTEND0: ATMEGA2560.18 ((OC2B)_PH6), CARRIAGE0.2
HOTEND1: ATMEGA2560.16 ((OC4B)_PH4), CARRIAGE1.2
HOTEND2: CARRIAGE2.2
HOTEND3: CARRIAGE3.2
LCDRESET: ATMEGA2560.47 ((ICP1)_PD4), LCD.1
LCDRX: ATMEGA2560.46 ((TXD1/INT3)_PD3), LCD.2
LCDTX: ATMEGA2560.45 ((RXD1/INT2)_PD2), LCD.3
LFAN0: ATMEGA2560.17 ((OC4C)_PH5), CARRIAGE0.3
LFAN1: ATMEGA2560.15 ((OC4A)_PH3), CARRIAGE1.3
LFAN2: CARRIAGE2.3
LFAN3: CARRIAGE3.3
MISO: ATMEGA2560.22 ((MISO/PCINT3)_PB3), ICSP.1, SD.3
MOSI: ATMEGA2560.21 ((MOSI/PCINT2)_PB2), ICSP.4, SD.2
unnamed: ATMEGA2560.33 (XTAL2), C1.1, R1.2, Y1.2
unnamed: ATMEGA2560.98 (AREF), C6.1
unnamed: ATMEGA2560.34 (XTAL1), C2.1, R1.1, Y1.1
unnamed: D1.C, L1.A (1), LM2595.2 (OUT)
unnamed: C21.1, L2.2, PTC1.2
unnamed: IC2.23 (CBUS0), TXLED.C
unnamed: IC2.22 (CBUS1), RXLED.C
unnamed: Q6.3 (D), RGBLEDS.2
unnamed: Q7.3 (D), RGBLEDS.3
unnamed: Q8.3 (D), RGBLEDS.4
unnamed: +24V.1, +24V1.1, F1.1
unnamed: Q2.1 (G), R16.1, R17.1
unnamed: D3.A, HOTBED.2, Q2.2 (D), R19.1
unnamed: LED2.C, R19.2
unnamed: C20.1, IC2.17 (3V3OUT)
unnamed: R33.1, TXLED.A
unnamed: R34.1, RXLED.A
unnamed: D8.A, L2.1
unnamed: PTC1.1, USB.1
unnamed: PWR24.C, R38.2
unnamed: PRW5.C, R39.2
PWM_HOTBED: ATMEGA2560.1 ((OC0B)_PG5), R16.2
R-PWM: ATMEGA2560.25 ((OC1B/PCINT6)_PB6), Q7.1 (G)
RX: IC2.1 (TXD), R35.2
RX0: ATMEGA2560.2 ((RXD0/PCINT8)_PE0), R35.1
SCL: ATMEGA2560.43 ((SCL/INT0)_PD0)
SCLK: ATMEGA2560.20 ((SCK/PCINT1)_PB1), ICSP.3, SD.4
SDA: ATMEGA2560.44 ((SDA/INT1)_PD1)
SDSS: ATMEGA2560.19 ((~SS/PCINT0)_PB0), SD.1
THERM0: ATMEGA2560.87 (PK2_(ADC10/PCINT18)), CARRIAGE0.1
THERM1: ATMEGA2560.88 (PK1_(ADC9/PCINT17)), CARRIAGE1.1
THERM2: ATMEGA2560.86 (PK3_(ADC11/PCINT19)), CARRIAGE2.1
THERM3: ATMEGA2560.85 (PK4_(ADC12/PCINT20)), CARRIAGE3.1
TX: IC2.5 (RXD), R36.2
TX0: ATMEGA2560.3 ((TXD0)_PE1), R36.1
USBD+: IC2.15 (USBDP), USB.3
USBD-: IC2.16 (USBDM), USB.2
USBSHIELD: L4.1, USB.5, USB.M1 (S1), USB.M2 (S2), USB.M3 (S3), USB.M4 (S4)
X0-!EN: ATMEGA2560.94 (PF3_(ADC3)), X0-AXIS.4
X0-STOP: ATMEGA2560.63 (PJ0_(RXD3/PCINT9)), ENDSTOPS.1
X1-!EN: ATMEGA2560.93 (PF4_(ADC4/TCK)), X1-AXIS.4
X1-STOP: ATMEGA2560.64 (PJ1_(TXD3/PCINT10)), ENDSTOPS.2 (1)
X2-!EN: ATMEGA2560.92 (PF5_(ADC5/TMS)), X2-AXIS.4
X2-STOP: ATMEGA2560.67 (PJ4_(PCINT13)), ENDSTOPS.5 (1)
X3-!EN: ATMEGA2560.91 (PF6_(ADC6/TDO)), X3-AXIS.4
X3-STOP: ATMEGA2560.68 (PJ5_(PCINT14)), ENDSTOPS.6 (1)
X-DIR: ATMEGA2560.95 (PF2_(ADC2)), X0-AXIS.5, X1-AXIS.5, X2-AXIS.5, X3-AXIS.5
X-STEP: ATMEGA2560.96 (PF1_(ADC1)), X0-AXIS.6, X1-AXIS.6, X2-AXIS.6, X3-AXIS.6
Y0-!EN: ATMEGA2560.6 ((OC3B/INT4)_PE4), Y0-AXIS.4
Y0-STOP: ATMEGA2560.65 (PJ2_(XCK3/PCINT11)), ENDSTOPS.3 (1)
Y1-!EN: ATMEGA2560.7 ((OC3C/INT5)_PE5), Y1-AXIS.4
Y1-STOP: ATMEGA2560.66 (PJ3_(PCINT12)), ENDSTOPS.4 (1)
Y-DIR: ATMEGA2560.5 ((OC3A/AIN1)_PE3), Y0-AXIS.5, Y1-AXIS.5
Y-STEP: ATMEGA2560.90 (PF7_(ADC7/TDI)), Y0-AXIS.6, Y1-AXIS.6
Z-!EN: ATMEGA2560.97 (PF0_(ADC0)), Z-AXIS.4
Z-DIR: ATMEGA2560.71 (PA7_(AD7)), Z-AXIS.5
Z-STEP: ATMEGA2560.72 (PA6_(AD6)), Z-AXIS.6
Z-STOP: ATMEGA2560.69 (PJ6_(PCINT15)), ENDSTOPS.7 (1)

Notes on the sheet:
Endstops
Power Output
Thermistors
USB COMUNICATION
ATmega2560
Power in to 5V
Power Supply
Display
TEST POINTS
FIDUCIALS
SD card Module
Extension Pin Header
4D Systems Display. Communication through serial.
RepRapBCN - Barcelona 2014 Marc Cobler Cosmen www.reprapbcn.com
Design based on the Megatronics V3.0 and SAV mkI. Released under the Creative Commons Attribution Share-Alike 3.0 License
Integrated 3D printer electronics for RepRap Machines.
Stepper outputs
The stepper drivers are integrated on the back of each stepper motor to improve EMC performance.
BCN3D++ Mother Board
RGB LEDs
Analog RGB LED strip - 3 PWM outputs needed Normally strips go to 12V but we have 24V in our board
Auto Leveling
